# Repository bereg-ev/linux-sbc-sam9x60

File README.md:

# linux-sbc-sam9x60

In 2019, when I finally decided to quit Eagle PCB and move over to KiCad, this small Linux single-board computer became my first real KiCad project.  

At the same time, it was the first time I tried JLCPCB’s PCBA service—a significant improvement in efficiency. Before that, all parts of my prototypes were fully hand-assembled by me, including all the R–C components and BGAs.  

Back then, JLC only offered top-side assembly, and the SAM9X60 CPU was not available, so I went for an unconventional placement: all parts on the top side except the CPU. This way I could hand-solder the 0.8 mm BGA at home with less risk of affecting the components on the other side.

<table>
  <tr>
    <td></td>
    <td></td>
  </tr>
  <tr>
    <td></td>
    <td></td>
  </tr>
</table>

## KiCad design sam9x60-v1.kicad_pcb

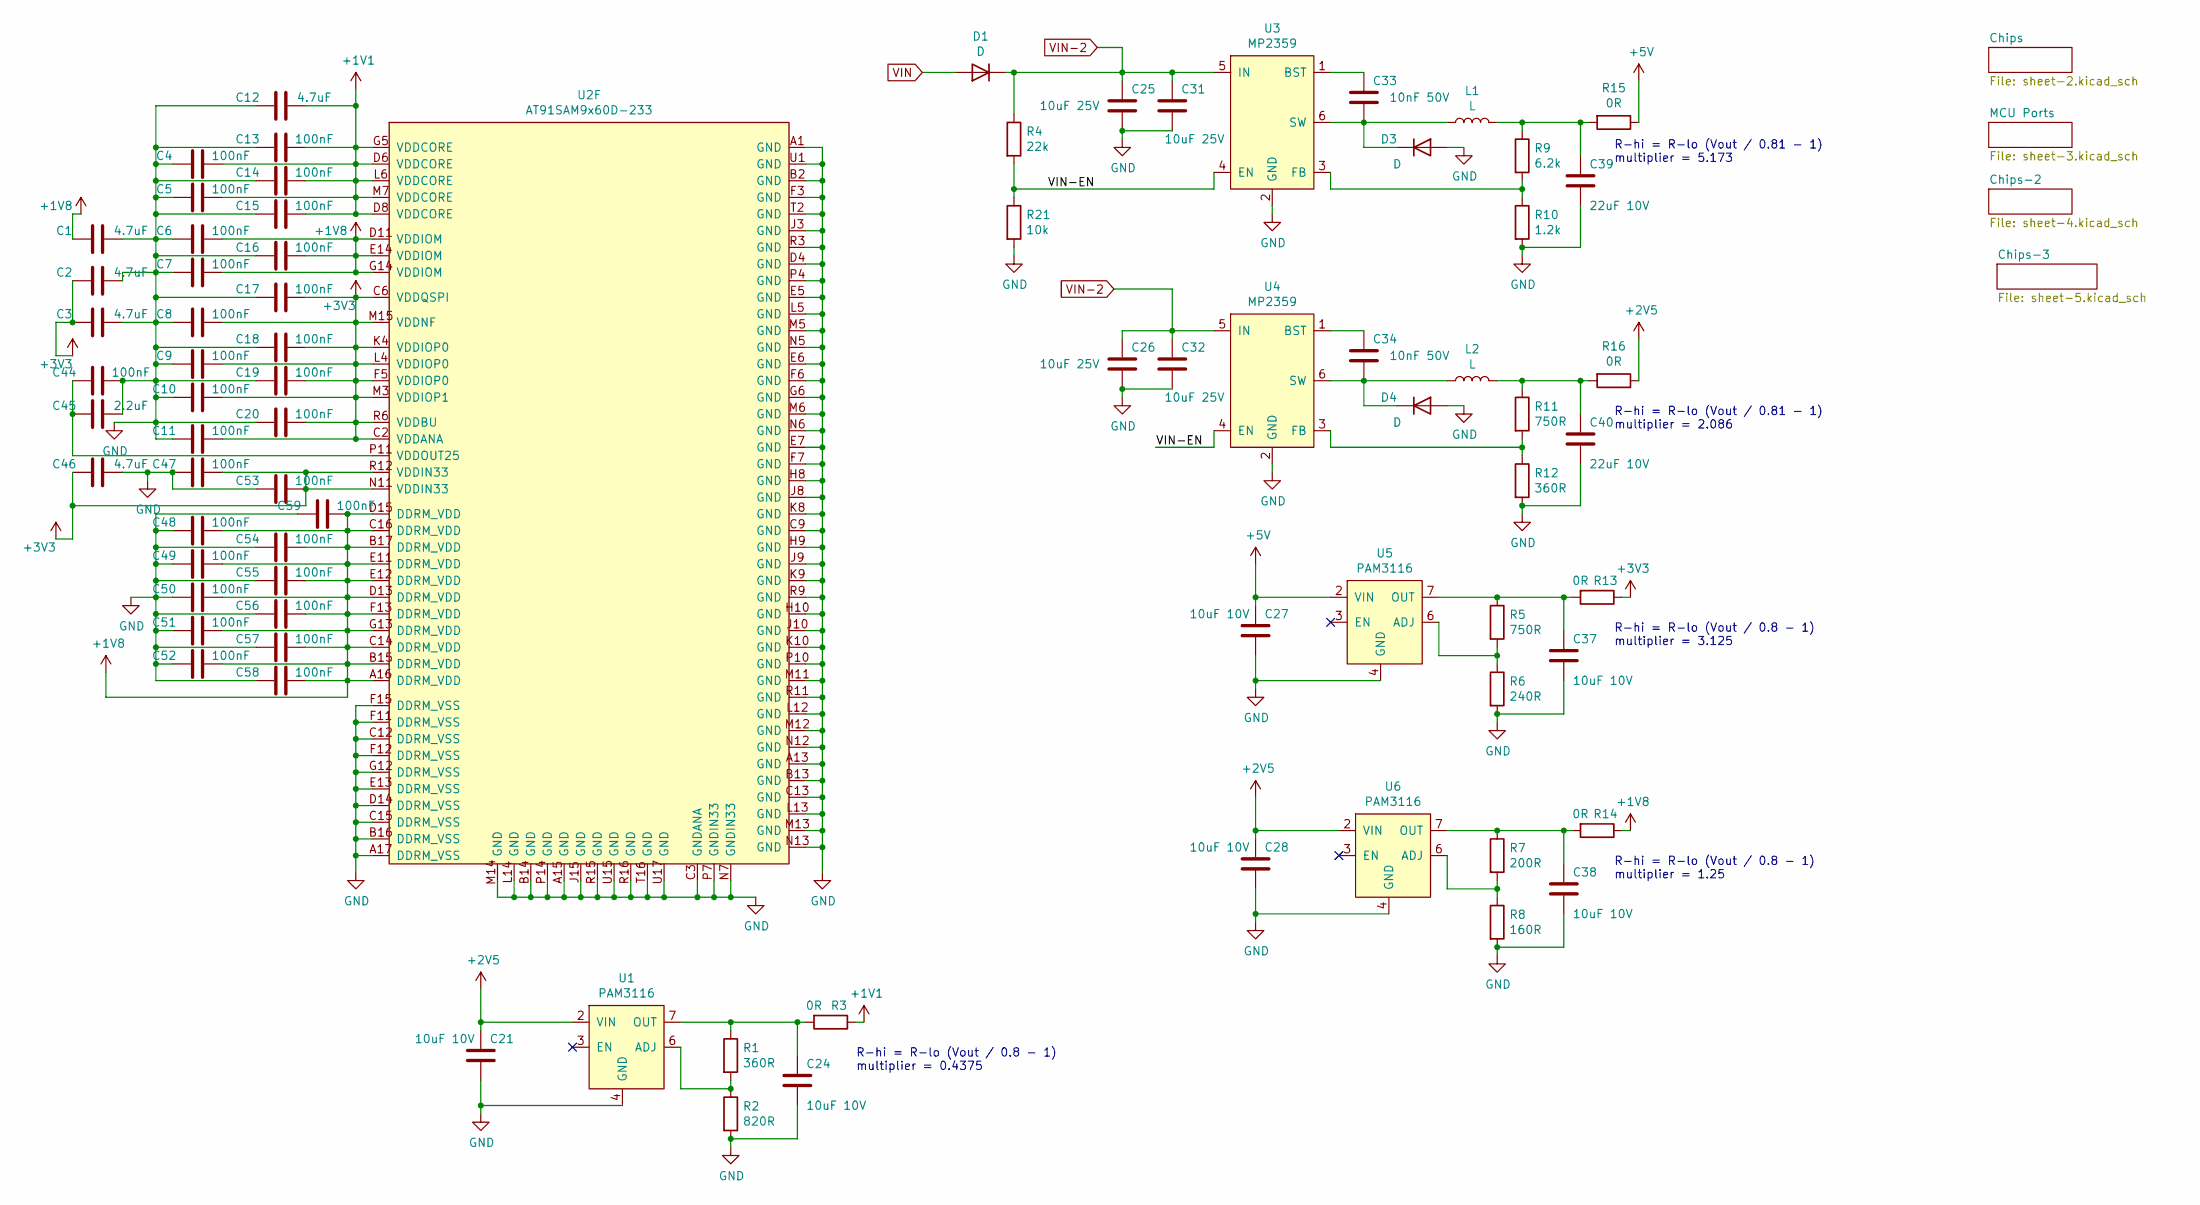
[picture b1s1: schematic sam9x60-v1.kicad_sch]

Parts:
C1, C2, C3, C12, C46: 4.7uF; C_0402_1005Metric; LCSC C23733
C4, C5, C6, C7, C8, C9, C10, C11, C13, C14, C15, C16, C17, C18, C19, C20, C44, C47, C48, C49, C50, C51, C52, C53, C54, C55, C56, C57, C58, C59: 100nF; C_0402_1005Metric; LCSC C1525
C21, C24, C27, C28, C37, C38: 10uF 10V; C_0603_1608Metric; LCSC C19702
C25, C26, C31, C32: 10uF 25V; C_0805_2012Metric; LCSC C15850
C33, C34: 10nF 50V; C_0603_1608Metric; LCSC C57112
C39, C40: 22uF 10V; C_0805_2012Metric; LCSC C45783
C45: 2.2uF; C_0603_1608Metric; LCSC C23630
D1, D3, D4: D; D_SMA; LCSC C14996
L1, L2: L; L-MWSA0402; LCSC C408337
R1, R12: 360R; R_0603_1608Metric; LCSC C25194
R2: 820R; R_0603_1608Metric; LCSC C23253
R3, R13, R14, R15, R16: 0R; R_0603_1608Metric; LCSC C21189
R4: 22k; R_0603_1608Metric; LCSC C31850
R5, R11: 750R; R_0603_1608Metric; LCSC C23241
R6: 240R; R_0603_1608Metric; LCSC C23350
R7: 200R; R_0603_1608Metric; LCSC C8218
R8: 160R; R_0603_1608Metric; LCSC C22814
R9: 6.2k; R_0603_1608Metric; LCSC C4260
R10: 1.2k; R_0603_1608Metric; LCSC C22765
R21: 10k; R_0603_1608Metric; LCSC C25804
U1, U5, U6: PAM3116; SOIC-8_3.9x4.9mm_P1.27mm; LCSC C481696
U2: AT91SAM9x60D-233; TFBGA-233
U3, U4: MP2359; SOT-23-6; LCSC C14259

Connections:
+1V1: C4.1, C5.1, C12.1, C13.1, C14.1, C15.1, R3.1, U2.D6 (VDDCORE), U2.D8 (VDDCORE), U2.G5 (VDDCORE), U2.L6 (VDDCORE), U2.M7 (VDDCORE); also elsewhere on the board
+1V8: C1.2, C6.1, C7.1, C16.1, C48.1, C49.1, C50.1, C51.1, C52.1, C54.1, C55.1, C56.1, C57.1, C58.1, C59.1, R14.1, U2.A16 (DDRM_VDD), U2.B15 (DDRM_VDD), U2.B17 (DDRM_VDD), U2.C14 (DDRM_VDD), U2.C16 (DDRM_VDD), U2.D11 (VDDIOM), U2.D13 (DDRM_VDD), U2.D15 (DDRM_VDD), U2.E11 (DDRM_VDD), U2.E12 (DDRM_VDD), U2.E14 (VDDIOM), U2.F13 (DDRM_VDD), U2.G13 (DDRM_VDD), U2.G14 (VDDIOM); also elsewhere on the board
+2V5: C21.1, C28.1, R16.1, U1.2 (VIN), U6.2 (VIN); also elsewhere on the board
+3V3: C2.2, C3.2, C8.1, C9.1, C10.1, C11.1, C17.1, C18.1, C19.1, C20.1, C46.2, C47.1, C53.1, R13.1, U2.C2 (VDDANA), U2.C6 (VDDQSPI), U2.F5 (VDDIOP0), U2.K4 (VDDIOP0), U2.L4 (VDDIOP0), U2.M3 (VDDIOP1), U2.M15 (VDDNF), U2.N11 (VDDIN33), U2.R6 (VDDBU), U2.R12 (VDDIN33); also elsewhere on the board
+5V: C27.1, R15.1, U5.2 (VIN); also elsewhere on the board
/VIN-EN: R4.2, R21.1, U3.4 (EN), U4.4 (EN)
GND: C1.1, C2.1, C3.1, C4.2, C5.2, C6.2, C7.2, C8.2, C9.2, C10.2, C11.2, C12.2, C13.2, C14.2, C15.2, C16.2, C17.2, C18.2, C19.2, C20.2, C21.2, C24.2, C25.2, C26.2, C27.2, C28.2, C31.2, C32.2, C37.2, C38.2, C39.2, C40.2, C44.1, C45.1, C46.1, C47.2, C48.2, C49.2, C50.2, C51.2, C52.2, C53.2, C54.2, C55.2, C56.2, C57.2, C58.2, C59.2, D3.2 (A), D4.2 (A), R2.2, R6.2, R8.2, R10.2, R12.2, R21.2, U1.4 (GND), U2.A1 (GND), U2.A13 (GND), U2.A15 (GND), U2.A17 (DDRM_VSS), U2.B2 (GND), U2.B13 (GND), U2.B14 (GND), U2.B16 (DDRM_VSS), U2.C3 (GNDANA), U2.C9 (GND), U2.C12 (DDRM_VSS), U2.C13 (GND), U2.C15 (DDRM_VSS), U2.D4 (GND), U2.D14 (DDRM_VSS), U2.E5 (GND), U2.E6 (GND), U2.E7 (GND), U2.E13 (DDRM_VSS), U2.F3 (GND), U2.F6 (GND), U2.F7 (GND), U2.F11 (DDRM_VSS), U2.F12 (DDRM_VSS), U2.F15 (DDRM_VSS), U2.G6 (GND), U2.G12 (DDRM_VSS), U2.H8 (GND), U2.H9 (GND), U2.H10 (GND), U2.J3 (GND), U2.J8 (GND), U2.J9 (GND), U2.J10 (GND), U2.J15 (GND), U2.K8 (GND), U2.K9 (GND), U2.K10 (GND), U2.L5 (GND), U2.L12 (GND), U2.L13 (GND), U2.L14 (GND), U2.M5 (GND), U2.M6 (GND), U2.M11 (GND), U2.M12 (GND), U2.M13 (GND), U2.M14 (GND), U2.N5 (GND), U2.N6 (GND), U2.N7 (GNDIN33), U2.N12 (GND), U2.N13 (GND), U2.P4 (GND), U2.P7 (GNDIN33), U2.P10 (GND), U2.P14 (GND), U2.R3 (GND), U2.R9 (GND), U2.R11 (GND), U2.R15 (GND), U2.R16 (GND), U2.T2 (GND), U2.T16 (GND), U2.U1 (GND), U2.U15 (GND), U2.U17 (GND), U3.2 (GND), U4.2 (GND), U5.4 (GND), U6.4 (GND); also elsewhere on the board
unnamed: C39.1, L1.2, R9.1, R15.2
unnamed: C40.1, L2.2, R11.1, R16.2
unnamed: C33.2, D3.1 (K), L1.1, U3.6 (SW)
unnamed: C34.2, D4.1 (K), L2.1, U4.6 (SW)
unnamed: R1.2, R2.1, U1.6 (ADJ)
unnamed: C24.1, R1.1, R3.2, U1.7 (OUT)
unnamed: C44.2, C45.2, U2.P11 (VDDOUT25)
unnamed: C33.1, U3.1 (BST)
unnamed: R9.2, R10.1, U3.3 (FB)
unnamed: C34.1, U4.1 (BST)
unnamed: R11.2, R12.1, U4.3 (FB)
unnamed: R5.2, R6.1, U5.6 (ADJ)
unnamed: C37.1, R5.1, R13.2, U5.7 (OUT)
unnamed: R7.2, R8.1, U6.6 (ADJ)
unnamed: C38.1, R7.1, R14.2, U6.7 (OUT)
VIN: D1.2 (A); also elsewhere on the board
VIN-2: C25.1, C26.1, C31.1, C32.1, D1.1 (K), R4.1, U3.5 (IN), U4.5 (IN)

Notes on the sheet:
R-hi = R-lo (Vout / 0.8 - 1) multiplier = 3.125
R-hi = R-lo (Vout / 0.8 - 1) multiplier = 0.4375
R-hi = R-lo (Vout / 0.81 - 1) multiplier = 2.086
R-hi = R-lo (Vout / 0.81 - 1) multiplier = 5.173
R-hi = R-lo (Vout / 0.8 - 1) multiplier = 1.25

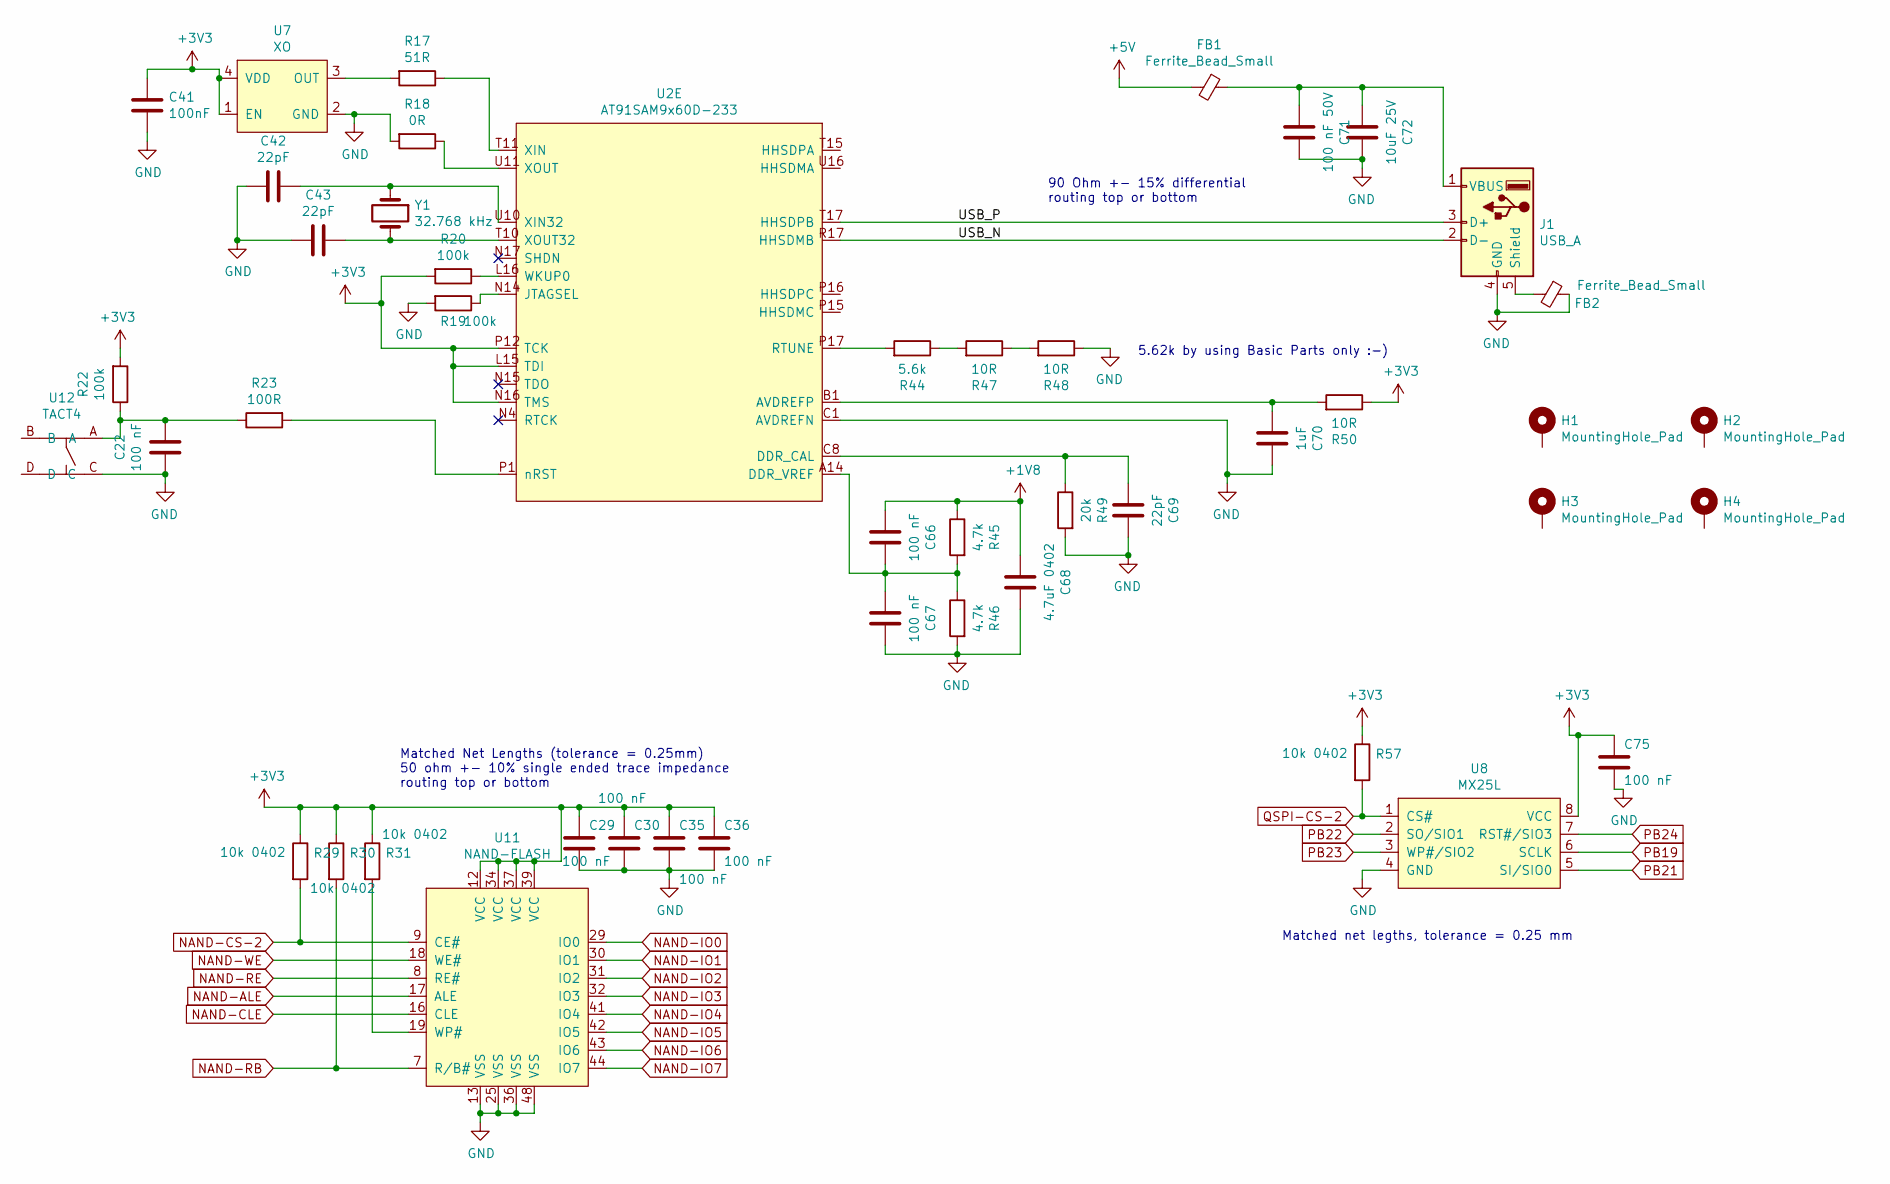
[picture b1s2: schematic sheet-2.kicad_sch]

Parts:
C22: 100 nF; C_0402_1005Metric
C29, C30, C35, C36, C66, C67, C75: 100 nF; C_0402_1005Metric; LCSC C1525
C41: 100nF; C_0402_1005Metric
C42, C43, C69: 22pF; C_0402_1005Metric; LCSC C1555
C68: 4.7uF 0402; C_0402_1005Metric; LCSC C23733
C70: 1uF; C_0402_1005Metric; LCSC C52923
C71: 100 nF 50V; C_0603_1608Metric; LCSC C57112
C72: 10uF 25V; C_0805_2012Metric; LCSC C15850
FB1, FB2: Ferrite_Bead_Small; R_0805_2012Metric; LCSC C1015
H1, H2, H3, H4: MountingHole_Pad; MountingHole_2.5mm_Pad_Via
J1: USB_A; USB_A_CONNFLY_DS1095-WNR0
R17: 51R; R_0603_1608Metric; LCSC C23197
R18: 0R; R_0603_1608Metric; LCSC C21189
R19, R20: 100k; R_0603_1608Metric; LCSC C25803
R22: 100k; R_0402_1005Metric; LCSC C25741
R23: 100R; R_0402_1005Metric; LCSC C25076
R29, R30, R31, R57: 10k 0402; R_0402_1005Metric; LCSC C25744
R44: 5.6k; R_0402_1005Metric; LCSC C25908
R45, R46: 4.7k; R_0402_1005Metric; LCSC C25900
R47, R48, R50: 10R; R_0402_1005Metric; LCSC C25077
R49: 20k; R_0402_1005Metric; LCSC C25765
U2: AT91SAM9x60D-233; TFBGA-233
U7: XO; Oscillator_SMD_EuroQuartz_XO32-4Pin_3.2x2.5mm; LCSC C295524
U8: MX25L; SOIC-8_5.23x5.23mm_P1.27mm; LCSC C71945
U11: NAND-FLASH; TSOP-I-48_18.4x12mm_P0.5mm; LCSC C92089
U12: TACT4; Tact-TS-551; LCSC C318887
Y1: 32.768 kHz; Crystal_SMD_3215-2Pin_3.2x1.5mm; LCSC C32346

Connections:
+1V8: C66.2, C68.2, R45.1; also elsewhere on the board
+3V3: C29.1, C30.1, C35.1, C36.1, C41.2, C75.1, R20.2, R22.2, R29.1, R30.1, R31.1, R50.1, R57.1, U2.L15 (TDI), U2.N16 (TMS), U2.P12 (TCK), U7.1 (EN), U7.4 (VDD), U8.8 (VCC), U11.12 (VCC), U11.34 (VCC), U11.37 (VCC), U11.39 (VCC); also elsewhere on the board
+5V: FB1.2; also elsewhere on the board
/Chips/USB_N: J1.2 (D-), U2.R17 (HHSDMB)
/Chips/USB_P: J1.3 (D+), U2.T17 (HHSDPB)
GND: C22.1, C29.2, C30.2, C35.2, C36.2, C41.1, C42.2, C43.2, C67.1, C68.1, C69.1, C70.1, C71.1, C72.1, C75.2, FB2.1, J1.4 (GND), R18.2, R19.2, R46.2, R48.1, R49.2, U2.C1 (AVDREFN), U7.2 (GND), U8.4 (GND), U11.13 (VSS), U11.25 (VSS), U11.36 (VSS), U11.48 (VSS), U12.C; also elsewhere on the board
NAND-ALE: U11.17 (ALE); also elsewhere on the board
NAND-CLE: U11.16 (CLE); also elsewhere on the board
NAND-CS-2: R29.2, U11.9 (CE#); also elsewhere on the board
NAND-IO0: U11.29 (IO0); also elsewhere on the board
NAND-IO1: U11.30 (IO1); also elsewhere on the board
NAND-IO2: U11.31 (IO2); also elsewhere on the board
NAND-IO3: U11.32 (IO3); also elsewhere on the board
NAND-IO4: U11.41 (IO4); also elsewhere on the board
NAND-IO5: U11.42 (IO5); also elsewhere on the board
NAND-IO6: U11.43 (IO6); also elsewhere on the board
NAND-IO7: U11.44 (IO7); also elsewhere on the board
NAND-RB: R30.2, U11.7 (R/B#); also elsewhere on the board
NAND-RE: U11.8 (RE#); also elsewhere on the board
NAND-WE: U11.18 (WE#); also elsewhere on the board
unnamed: C22.2, R22.1, R23.1, U12.A
unnamed: FB2.2, J1.5 (Shield)
unnamed: C71.2, C72.2, FB1.1, J1.1 (VBUS)
unnamed: R44.1, R47.2
unnamed: R47.1, R48.2
unnamed: C70.2, R50.2, U2.B1 (AVDREFP)
unnamed: C69.2, R49.1, U2.C8 (DDR_CAL)
unnamed: C66.1, C67.2, R45.2, R46.1, U2.A14 (DDR_VREF)
unnamed: R19.1, U2.N14 (JTAGSEL)
unnamed: R44.2, U2.P17 (RTUNE)
unnamed: R20.1, U2.L16 (WKUP0)
unnamed: C42.1, U2.U10 (XIN32), Y1.1
unnamed: R17.1, U2.T11 (XIN)
unnamed: C43.1, U2.T10 (XOUT32), Y1.2
unnamed: R18.1, U2.U11 (XOUT)
unnamed: R23.2, U2.P1 (nRST)
unnamed: R17.2, U7.3 (OUT)
unnamed: R31.2, U11.19 (WP#)
PB19: U8.6 (SCLK); also elsewhere on the board
PB21: U8.5 (SI/SIO0); also elsewhere on the board
PB22: U8.2 (SO/SIO1); also elsewhere on the board
PB23: U8.3 (WP#/SIO2); also elsewhere on the board
PB24: U8.7 (RST#/SIO3); also elsewhere on the board
QSPI-CS-2: R57.2, U8.1 (CS#)

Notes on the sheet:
Matched net legths, tolerance = 0.25 mm
5.62k by using Basic Parts only :-)
90 Ohm +- 15% differential routing top or bottom
Matched Net Lengths (tolerance = 0.25mm) 50 ohm +- 10% single ended trace impedance routing top or bottom

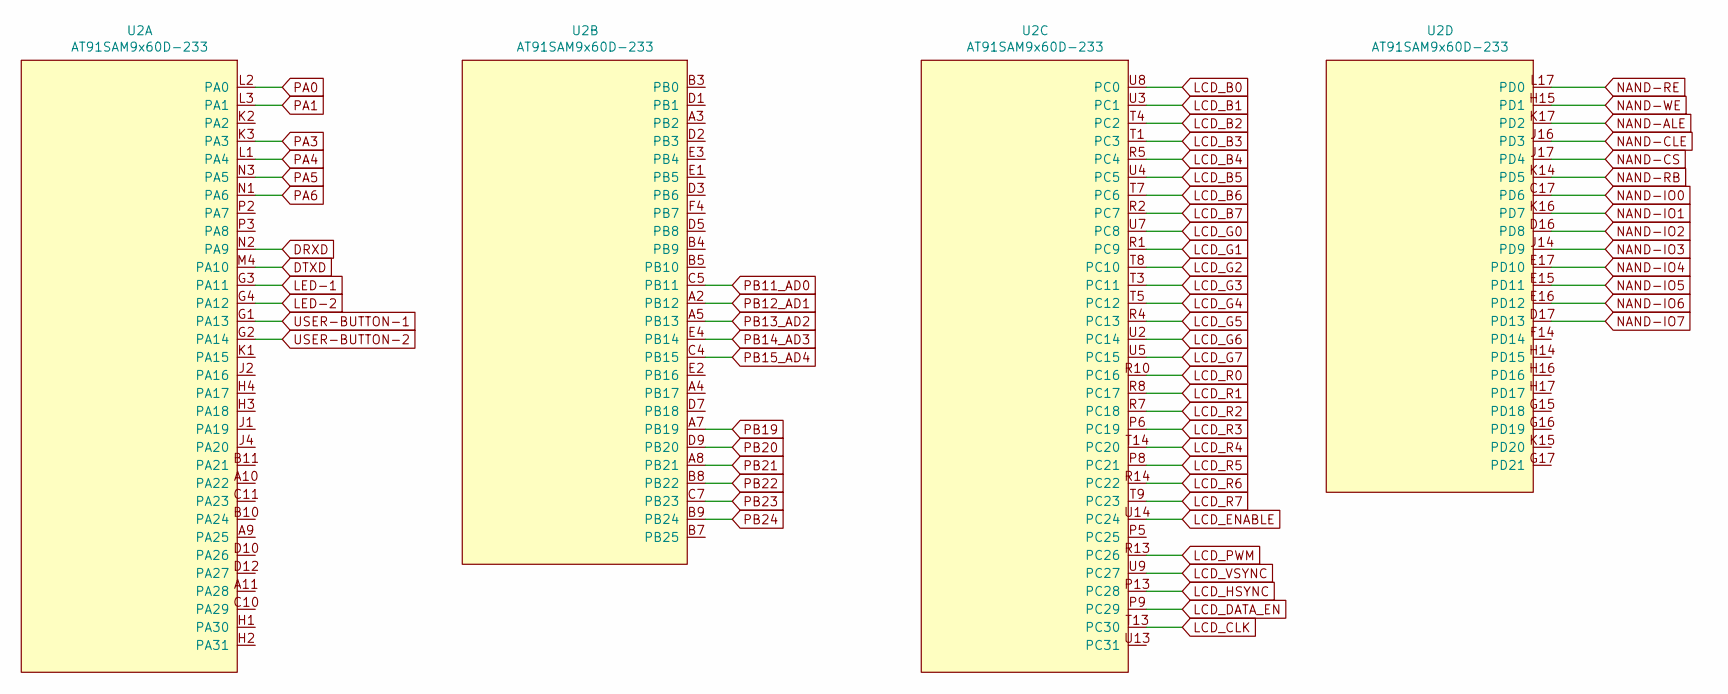
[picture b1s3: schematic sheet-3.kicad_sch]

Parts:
U2: AT91SAM9x60D-233

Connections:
DRXD: U2.N2 (PA9); also elsewhere on the board
DTXD: U2.M4 (PA10); also elsewhere on the board
LCD_B0: U2.U8 (PC0); also elsewhere on the board
LCD_B1: U2.U3 (PC1); also elsewhere on the board
LCD_B2: U2.T4 (PC2); also elsewhere on the board
LCD_B3: U2.T1 (PC3); also elsewhere on the board
LCD_B4: U2.R5 (PC4); also elsewhere on the board
LCD_B5: U2.U4 (PC5); also elsewhere on the board
LCD_B6: U2.T7 (PC6); also elsewhere on the board
LCD_B7: U2.R2 (PC7); also elsewhere on the board
LCD_CLK: U2.T13 (PC30); also elsewhere on the board
LCD_DATA_EN: U2.P9 (PC29); also elsewhere on the board
LCD_ENABLE: U2.U14 (PC24); also elsewhere on the board
LCD_G0: U2.U7 (PC8); also elsewhere on the board
LCD_G1: U2.R1 (PC9); also elsewhere on the board
LCD_G2: U2.T8 (PC10); also elsewhere on the board
LCD_G3: U2.T3 (PC11); also elsewhere on the board
LCD_G4: U2.T5 (PC12); also elsewhere on the board
LCD_G5: U2.R4 (PC13); also elsewhere on the board
LCD_G6: U2.U2 (PC14); also elsewhere on the board
LCD_G7: U2.U5 (PC15); also elsewhere on the board
LCD_HSYNC: U2.P13 (PC28); also elsewhere on the board
LCD_PWM: U2.R13 (PC26); also elsewhere on the board
LCD_R0: U2.R10 (PC16); also elsewhere on the board
LCD_R1: U2.R8 (PC17); also elsewhere on the board
LCD_R2: U2.R7 (PC18); also elsewhere on the board
LCD_R3: U2.P6 (PC19); also elsewhere on the board
LCD_R4: U2.T14 (PC20); also elsewhere on the board
LCD_R5: U2.P8 (PC21); also elsewhere on the board
LCD_R6: U2.R14 (PC22); also elsewhere on the board
LCD_R7: U2.T9 (PC23); also elsewhere on the board
LCD_VSYNC: U2.U9 (PC27); also elsewhere on the board
LED-1: U2.G3 (PA11); also elsewhere on the board
LED-2: U2.G4 (PA12); also elsewhere on the board
NAND-ALE: U2.K17 (PD2); also elsewhere on the board
NAND-CLE: U2.J16 (PD3); also elsewhere on the board
NAND-CS: U2.J17 (PD4); also elsewhere on the board
NAND-IO0: U2.C17 (PD6); also elsewhere on the board
NAND-IO1: U2.K16 (PD7); also elsewhere on the board
NAND-IO2: U2.D16 (PD8); also elsewhere on the board
NAND-IO3: U2.J14 (PD9); also elsewhere on the board
NAND-IO4: U2.E17 (PD10); also elsewhere on the board
NAND-IO5: U2.E15 (PD11); also elsewhere on the board
NAND-IO6: U2.E16 (PD12); also elsewhere on the board
NAND-IO7: U2.D17 (PD13); also elsewhere on the board
NAND-RB: U2.K14 (PD5); also elsewhere on the board
NAND-RE: U2.L17 (PD0); also elsewhere on the board
NAND-WE: U2.H15 (PD1); also elsewhere on the board
PA0: U2.L2 (PA0); also elsewhere on the board
PA1: U2.L3 (PA1); also elsewhere on the board
PA3: U2.K3 (PA3); also elsewhere on the board
PA4: U2.L1 (PA4); also elsewhere on the board
PA5: U2.N3 (PA5); also elsewhere on the board
PA6: U2.N1 (PA6); also elsewhere on the board
PB11_AD0: U2.C5 (PB11); also elsewhere on the board
PB12_AD1: U2.A2 (PB12); also elsewhere on the board
PB13_AD2: U2.A5 (PB13); also elsewhere on the board
PB14_AD3: U2.E4 (PB14); also elsewhere on the board
PB15_AD4: U2.C4 (PB15); also elsewhere on the board
PB19: U2.A7 (PB19); also elsewhere on the board
PB20: U2.D9 (PB20); also elsewhere on the board
PB21: U2.A8 (PB21); also elsewhere on the board
PB22: U2.B8 (PB22); also elsewhere on the board
PB23: U2.C7 (PB23); also elsewhere on the board
PB24: U2.B9 (PB24); also elsewhere on the board
USER-BUTTON-1: U2.G1 (PA13); also elsewhere on the board
USER-BUTTON-2: U2.G2 (PA14); also elsewhere on the board

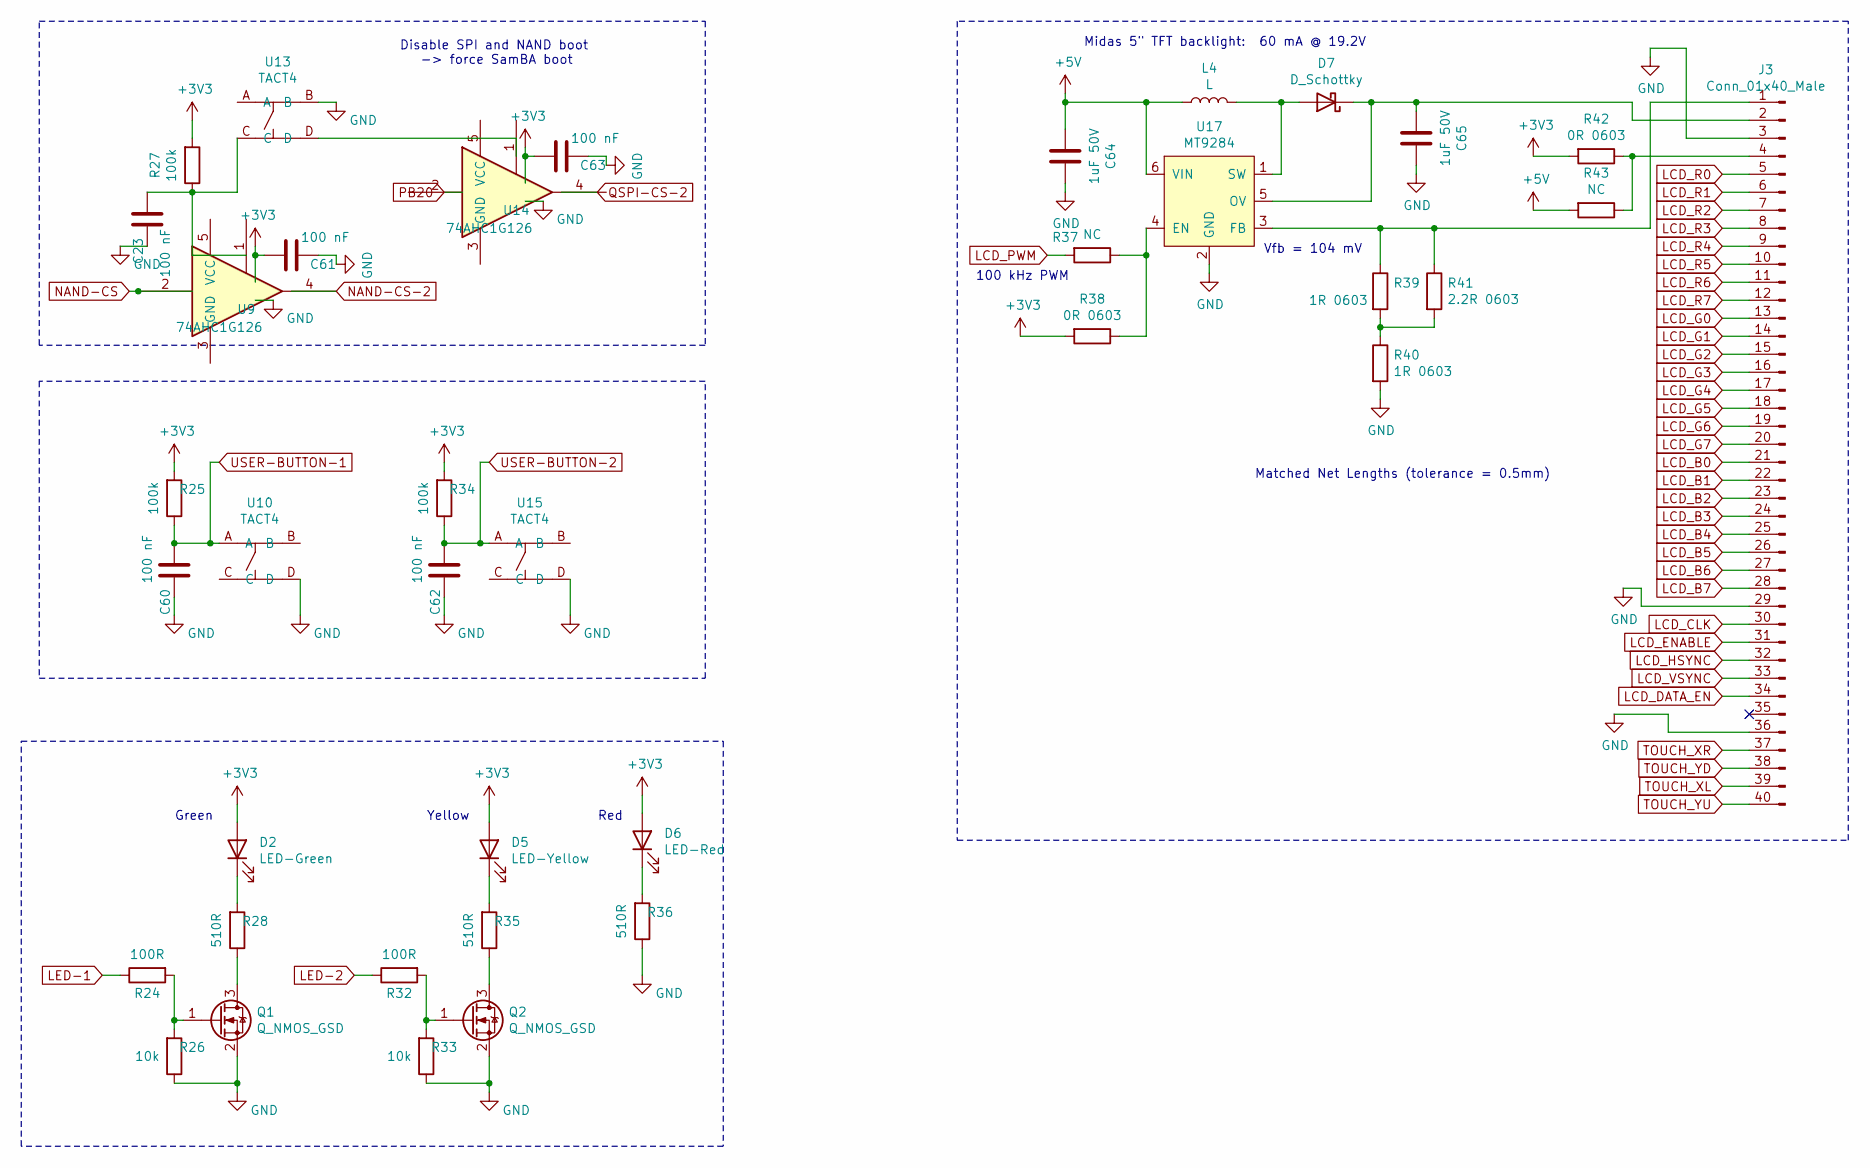
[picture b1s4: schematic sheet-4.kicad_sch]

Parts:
C23, C60, C61, C62, C63: 100 nF; C_0402_1005Metric; LCSC C1525
C64, C65: 1uF 50V; C_0603_1608Metric; LCSC C15849
D2: LED-Green; R_0603_1608Metric; LCSC C72043
D5: LED-Yellow; R_0603_1608Metric; LCSC C72038
D6: LED-Red; R_0603_1608Metric; LCSC C2286
D7: D_Schottky; D_SOD-123; LCSC C8598
J3: Conn_01x40_Male; Hirose_FH12-40S-0.5SH_1x40-1MP_P0.50mm_Horizontal
L4: L; L-MWSA0402; LCSC C408337
Q1, Q2: Q_NMOS_GSD; TSOT-23; LCSC C8545
R24, R32: 100R; R_0402_1005Metric; LCSC C25076
R25, R34: 100k; R_0603_1608Metric; LCSC C25803
R26, R33: 10k; R_0402_1005Metric; LCSC C25744
R27: 100k; R_0402_1005Metric; LCSC C25741
R28, R35, R36: 510R; R_0603_1608Metric; LCSC C23193
R37, R43: NC; R_0603_1608Metric
R38, R42: 0R 0603; R_0603_1608Metric; LCSC C21189
R39, R40: 1R 0603; R_0603_1608Metric; LCSC C22936
R41: 2.2R 0603; R_0603_1608Metric; LCSC C22939
U9, U14: 74AHC1G126; SOT-353_SC-70-5; LCSC C92637
U10, U13, U15: TACT4; Tact-TS-551; LCSC C318887
U17: MT9284; SOT-23-6; LCSC C181780

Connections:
+3V3: C61.2, C63.2, D2.2 (A), D5.2 (A), D6.2 (A), R25.2, R27.2, R34.2, R38.2, R42.2; also elsewhere on the board
+5V: C64.2, L4.1, R43.2, U17.6 (VIN); also elsewhere on the board
GND: C23.1, C60.1, C61.1, C62.1, C63.1, C64.1, C65.1, J3.3, J3.29, J3.36, Q1.2 (S), Q2.2 (S), R26.1, R33.1, R36.1, R40.2, U10.D, U13.B, U15.D, U17.2 (GND); also elsewhere on the board
LCD_B0: J3.21; also elsewhere on the board
LCD_B1: J3.22; also elsewhere on the board
LCD_B2: J3.23; also elsewhere on the board
LCD_B3: J3.24; also elsewhere on the board
LCD_B4: J3.25; also elsewhere on the board
LCD_B5: J3.26; also elsewhere on the board
LCD_B6: J3.27; also elsewhere on the board
LCD_B7: J3.28; also elsewhere on the board
LCD_CLK: J3.30; also elsewhere on the board
LCD_DATA_EN: J3.34; also elsewhere on the board
LCD_ENABLE: J3.31; also elsewhere on the board
LCD_G0: J3.13; also elsewhere on the board
LCD_G1: J3.14; also elsewhere on the board
LCD_G2: J3.15; also elsewhere on the board
LCD_G3: J3.16; also elsewhere on the board
LCD_G4: J3.17; also elsewhere on the board
LCD_G5: J3.18; also elsewhere on the board
LCD_G6: J3.19; also elsewhere on the board
LCD_G7: J3.20; also elsewhere on the board
LCD_HSYNC: J3.32; also elsewhere on the board
LCD_PWM: R37.2; also elsewhere on the board
LCD_R0: J3.5; also elsewhere on the board
LCD_R1: J3.6; also elsewhere on the board
LCD_R2: J3.7; also elsewhere on the board
LCD_R3: J3.8; also elsewhere on the board
LCD_R4: J3.9; also elsewhere on the board
LCD_R5: J3.10; also elsewhere on the board
LCD_R6: J3.11; also elsewhere on the board
LCD_R7: J3.12; also elsewhere on the board
LCD_VSYNC: J3.33; also elsewhere on the board
LED-1: R24.1; also elsewhere on the board
LED-2: R32.1; also elsewhere on the board
NAND-CS: U9.2; also elsewhere on the board
NAND-CS-2: U9.4; also elsewhere on the board
unnamed: C23.2, R27.1, U13.C
unnamed: D2.1 (K), R28.2
unnamed: D5.1 (K), R35.2
unnamed: D6.1 (K), R36.2
unnamed: D7.2 (A), L4.2, U17.1 (SW)
unnamed: C65.2, D7.1 (K), J3.2, U17.5 (OV)
unnamed: J3.1, R39.1, R41.1, U17.3 (FB)
unnamed: J3.4, R42.1, R43.1
unnamed: Q1.3 (D), R28.1
unnamed: Q1.1 (G), R24.2, R26.2
unnamed: Q2.3 (D), R35.1
unnamed: Q2.1 (G), R32.2, R33.2
unnamed: R39.2, R40.1, R41.2
unnamed: R37.1, R38.1, U17.4 (EN)
TOUCH_XL: J3.39; also elsewhere on the board
TOUCH_XR: J3.37; also elsewhere on the board
TOUCH_YD: J3.38; also elsewhere on the board
TOUCH_YU: J3.40; also elsewhere on the board
USER-BUTTON-1: C60.2, R25.1, U10.A; also elsewhere on the board
USER-BUTTON-2: C62.2, R34.1, U15.A; also elsewhere on the board

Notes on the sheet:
Matched Net Lengths (tolerance = 0.5mm)
Midas 5" TFT backlight: 60 mA @ 19.2V
Yellow
Disable SPI and NAND boot -> force SamBA boot
Vfb = 104 mV
Green
Red
100 kHz PWM

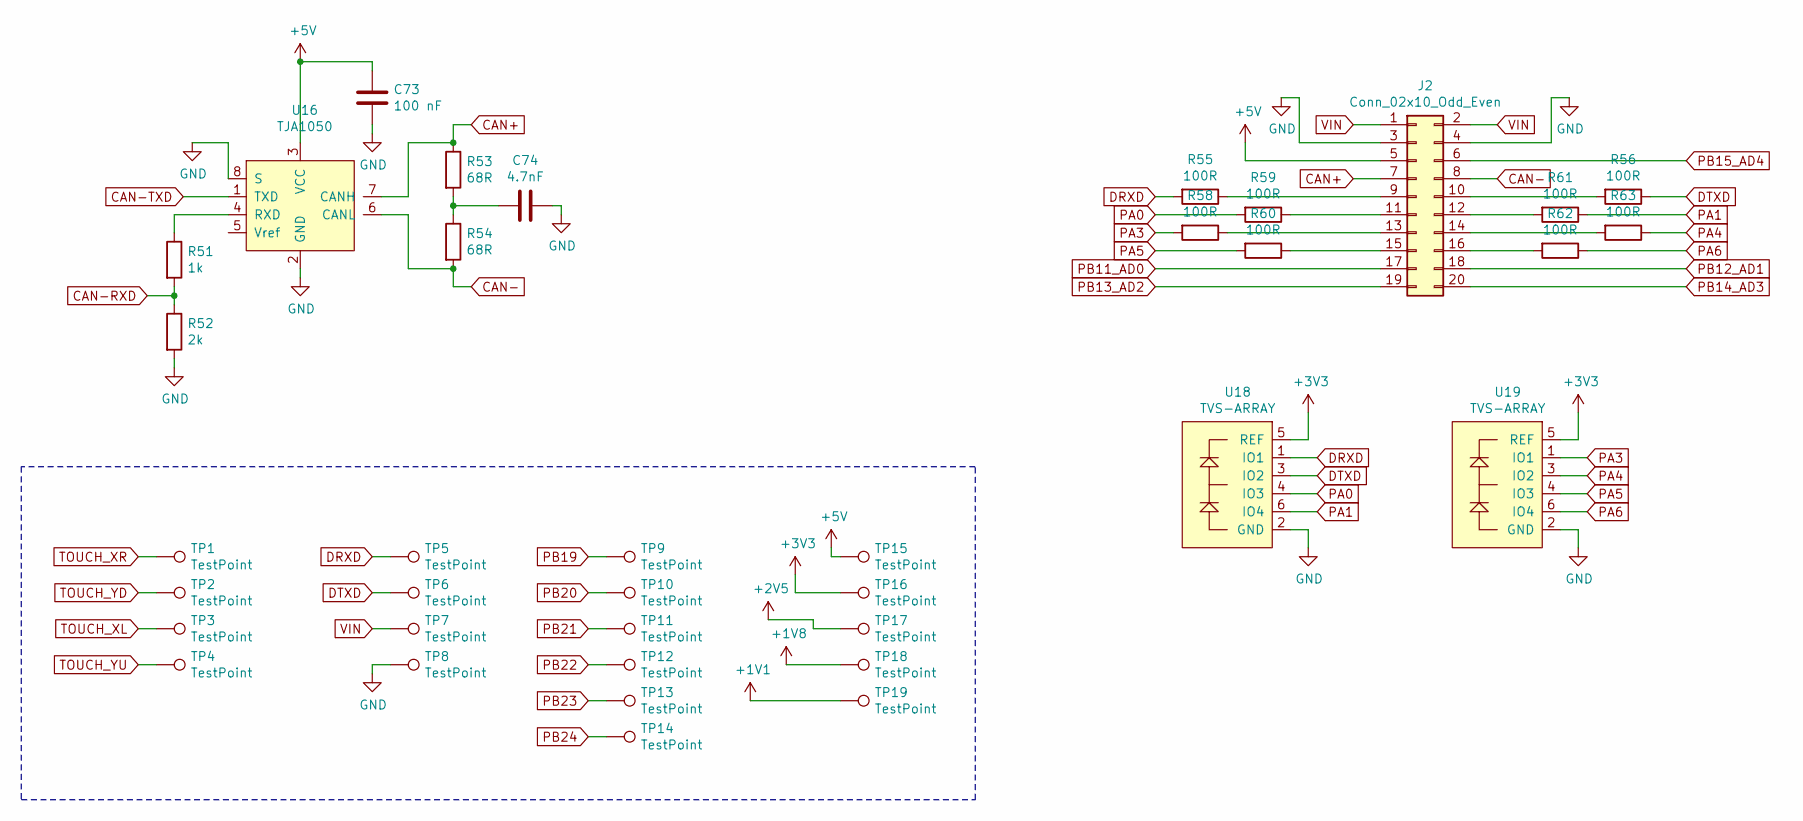
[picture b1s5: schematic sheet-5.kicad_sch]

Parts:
C73: 100 nF; R_0402_1005Metric; LCSC C1525
C74: 4.7nF; R_0603_1608Metric; LCSC C53987
J2: Conn_02x10_Odd_Even; PinHeader_2x10_P2.54mm_Vertical
R51: 1k; R_0402_1005Metric; LCSC C11702
R52: 2k; R_0402_1005Metric; LCSC C4109
R53, R54: 68R; R_0805_2012Metric; LCSC C17802
R55, R56, R58, R59, R60, R61, R62, R63: 100R; R_0603_1608Metric; LCSC C22775
TP1, TP2, TP3, TP4, TP5, TP6, TP7, TP8, TP9, TP10, TP11, TP12, TP13, TP14, TP15, TP16, TP17, TP18, TP19: TestPoint; TestPoint_Pad_D1.5mm
U16: TJA1050; SOIC-8_3.9x4.9mm_P1.27mm; LCSC C6952
U18, U19: TVS-ARRAY; SOT-23-6; LCSC C85364

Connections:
+1V1: TP19.1; also elsewhere on the board
+1V8: TP18.1; also elsewhere on the board
+2V5: TP17.1; also elsewhere on the board
+3V3: TP16.1, U18.5 (REF), U19.5 (REF); also elsewhere on the board
+5V: C73.2, J2.5, TP15.1, U16.3 (VCC); also elsewhere on the board
CAN+: J2.7, R53.1, U16.7 (CANH)
CAN-: J2.8, R54.2, U16.6 (CANL)
CAN-RXD: R51.2, R52.1
CAN-TXD: U16.1 (TXD)
DRXD: R55.2, TP5.1, U18.1 (IO1); also elsewhere on the board
DTXD: R56.1, TP6.1, U18.3 (IO2); also elsewhere on the board
GND: C73.1, C74.1, J2.3, J2.4, R52.2, TP8.1, U16.2 (GND), U16.8 (S), U18.2 (GND), U19.2 (GND); also elsewhere on the board
unnamed: C74.2, R53.2, R54.1
unnamed: J2.9, R55.1
unnamed: J2.10, R56.2
unnamed: J2.11, R59.1
unnamed: J2.12, R61.2
unnamed: J2.13, R58.1
unnamed: J2.14, R63.2
unnamed: J2.15, R60.1
unnamed: J2.16, R62.2
unnamed: R51.1, U16.4 (RXD)
PA0: R59.2, U18.4 (IO3); also elsewhere on the board
PA1: R61.1, U18.6 (IO4); also elsewhere on the board
PA3: R58.2, U19.1 (IO1); also elsewhere on the board
PA4: R63.1, U19.3 (IO2); also elsewhere on the board
PA5: R60.2, U19.4 (IO3); also elsewhere on the board
PA6: R62.1, U19.6 (IO4); also elsewhere on the board
PB11_AD0: J2.17; also elsewhere on the board
PB12_AD1: J2.18; also elsewhere on the board
PB13_AD2: J2.19; also elsewhere on the board
PB14_AD3: J2.20; also elsewhere on the board
PB15_AD4: J2.6; also elsewhere on the board
PB19: TP9.1; also elsewhere on the board
PB20: TP10.1; also elsewhere on the board
PB21: TP11.1; also elsewhere on the board
PB22: TP12.1; also elsewhere on the board
PB23: TP13.1; also elsewhere on the board
PB24: TP14.1; also elsewhere on the board
TOUCH_XL: TP3.1; also elsewhere on the board
TOUCH_XR: TP1.1; also elsewhere on the board
TOUCH_YD: TP2.1; also elsewhere on the board
TOUCH_YU: TP4.1; also elsewhere on the board
VIN: J2.1, J2.2, TP7.1; also elsewhere on the board

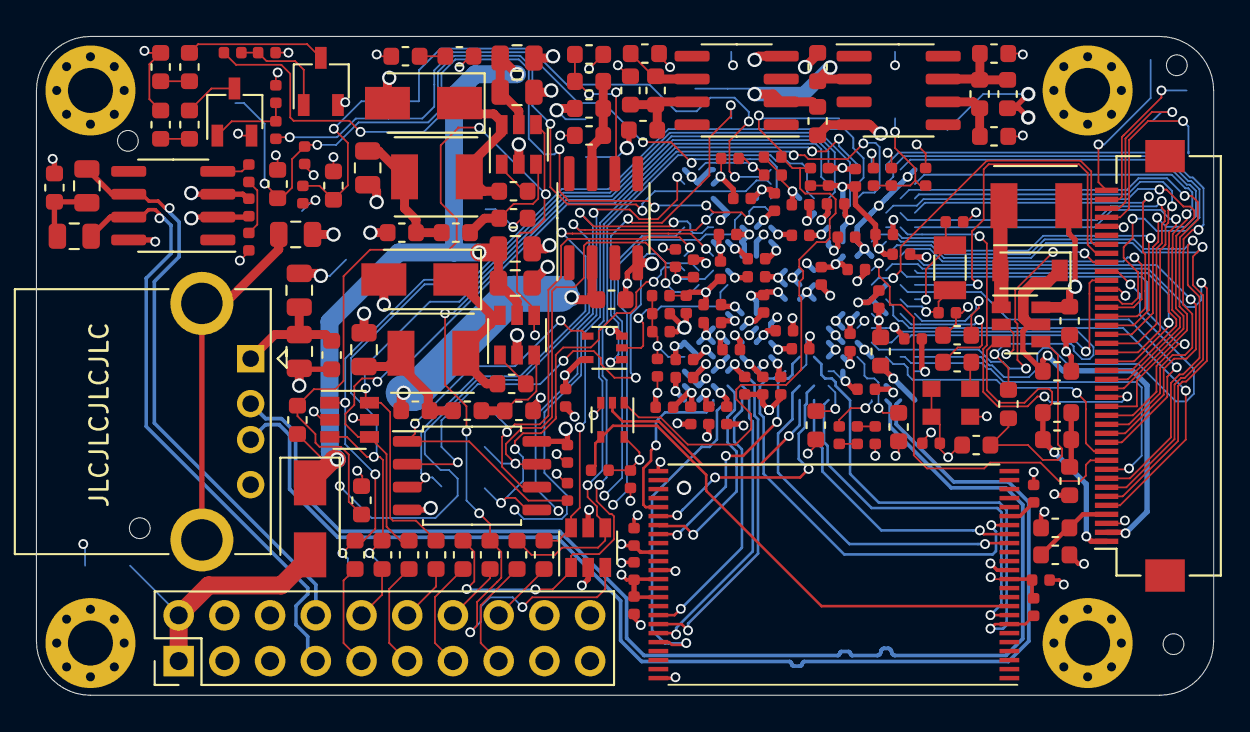
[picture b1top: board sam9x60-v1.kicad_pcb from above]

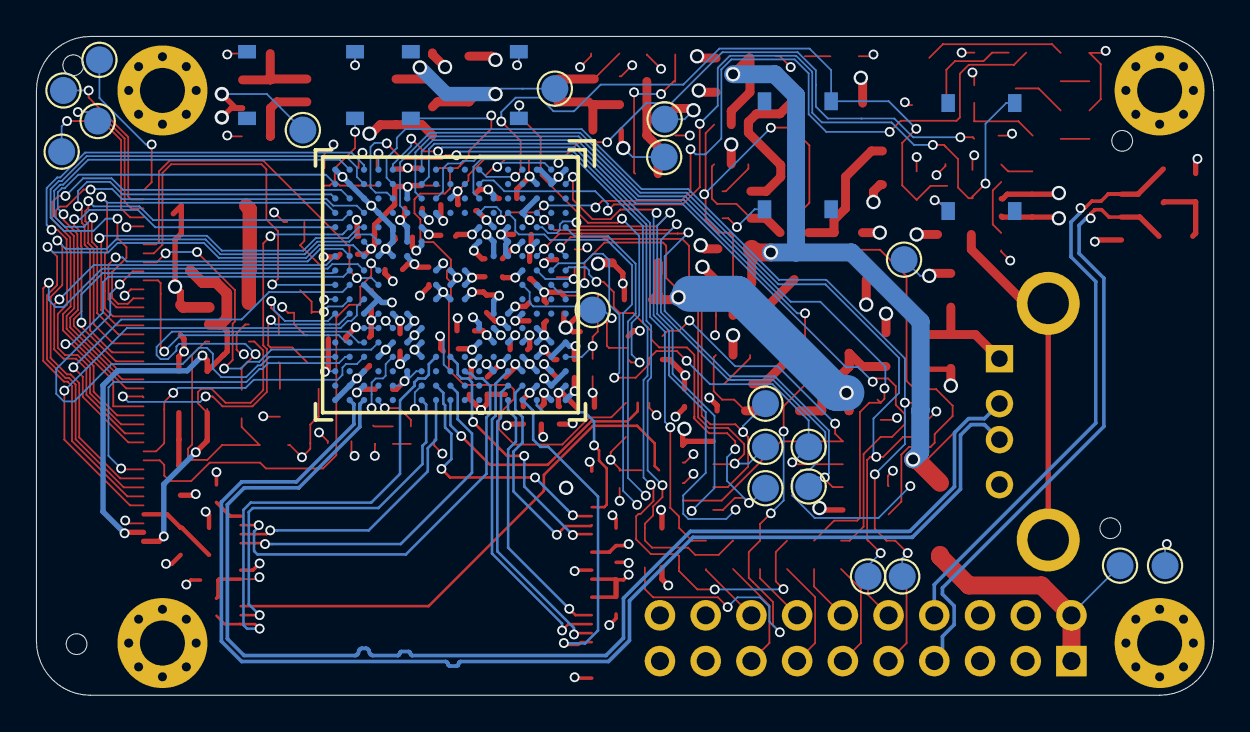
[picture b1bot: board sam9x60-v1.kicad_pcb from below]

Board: 4 copper layers, 65.4 x 36.6 mm, 198 parts (24 on the bottom side), 144 nets.

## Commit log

2026-06-18 initial commit: JTAGSEL fix, updated sch + brd in Kicad 7, board layer images and photo of the physical board with a coin
2026-06-18 README with project history and images
    Added detailed project background and assembly process.
